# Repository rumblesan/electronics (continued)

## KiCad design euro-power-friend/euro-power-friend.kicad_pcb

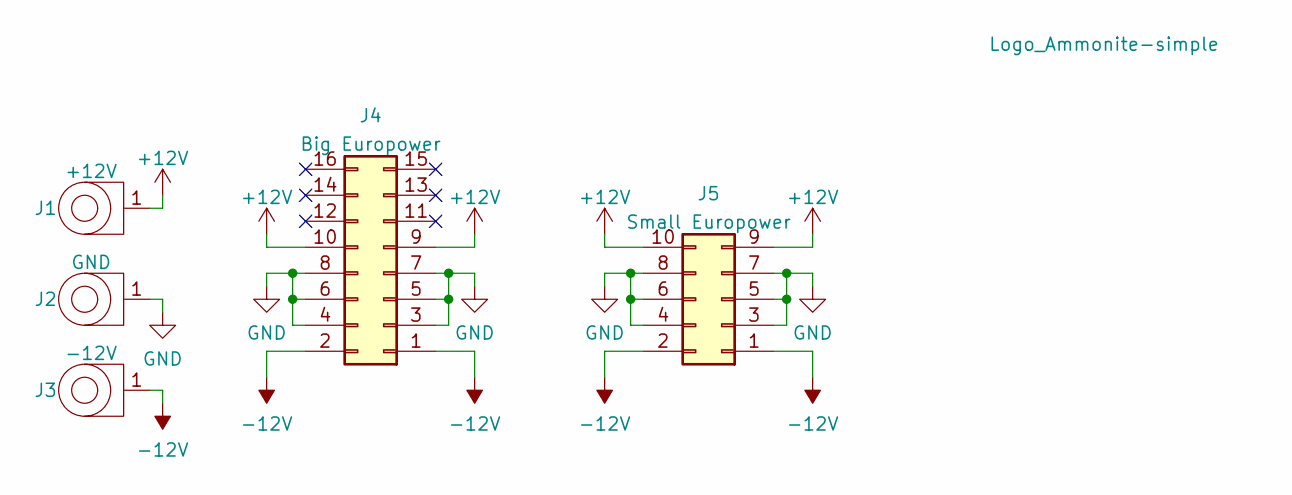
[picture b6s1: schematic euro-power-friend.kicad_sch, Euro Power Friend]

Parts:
H1: Logo_Ammonite-simple; Logo_Ammonite-simple_10.4mmx12.0mm
J1: +12V; Deltron_571_PCB_BananaJack
J2: GND; Deltron_571_PCB_BananaJack
J3: -12V; Deltron_571_PCB_BananaJack
J4: Big Europower; EurorackPowerHeader_2x08_P2.54mm_Shrouded
J5: Small Europower; EurorackPowerHeader_2x05_P2.54mm_Shrouded

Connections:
+12V: J1.1, J4.9, J4.10, J5.9, J5.10
-12V: J3.1, J4.1, J4.2, J5.1, J5.2
GND: J2.1, J4.3, J4.4, J4.5, J4.6, J4.7, J4.8, J5.3, J5.4, J5.5, J5.6, J5.7, J5.8

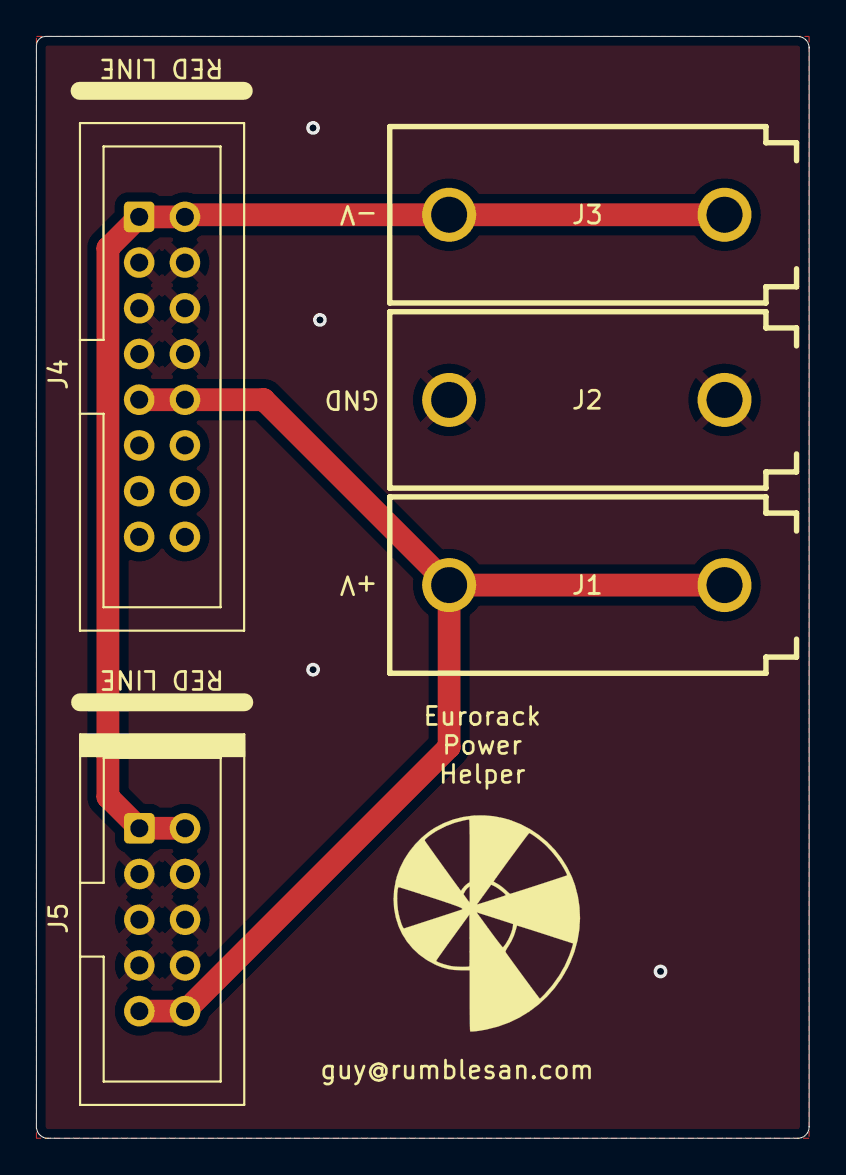
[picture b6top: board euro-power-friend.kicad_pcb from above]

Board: 2 copper layers, 42.9 x 61.2 mm, 6 parts (0 on the bottom side), 3 nets.

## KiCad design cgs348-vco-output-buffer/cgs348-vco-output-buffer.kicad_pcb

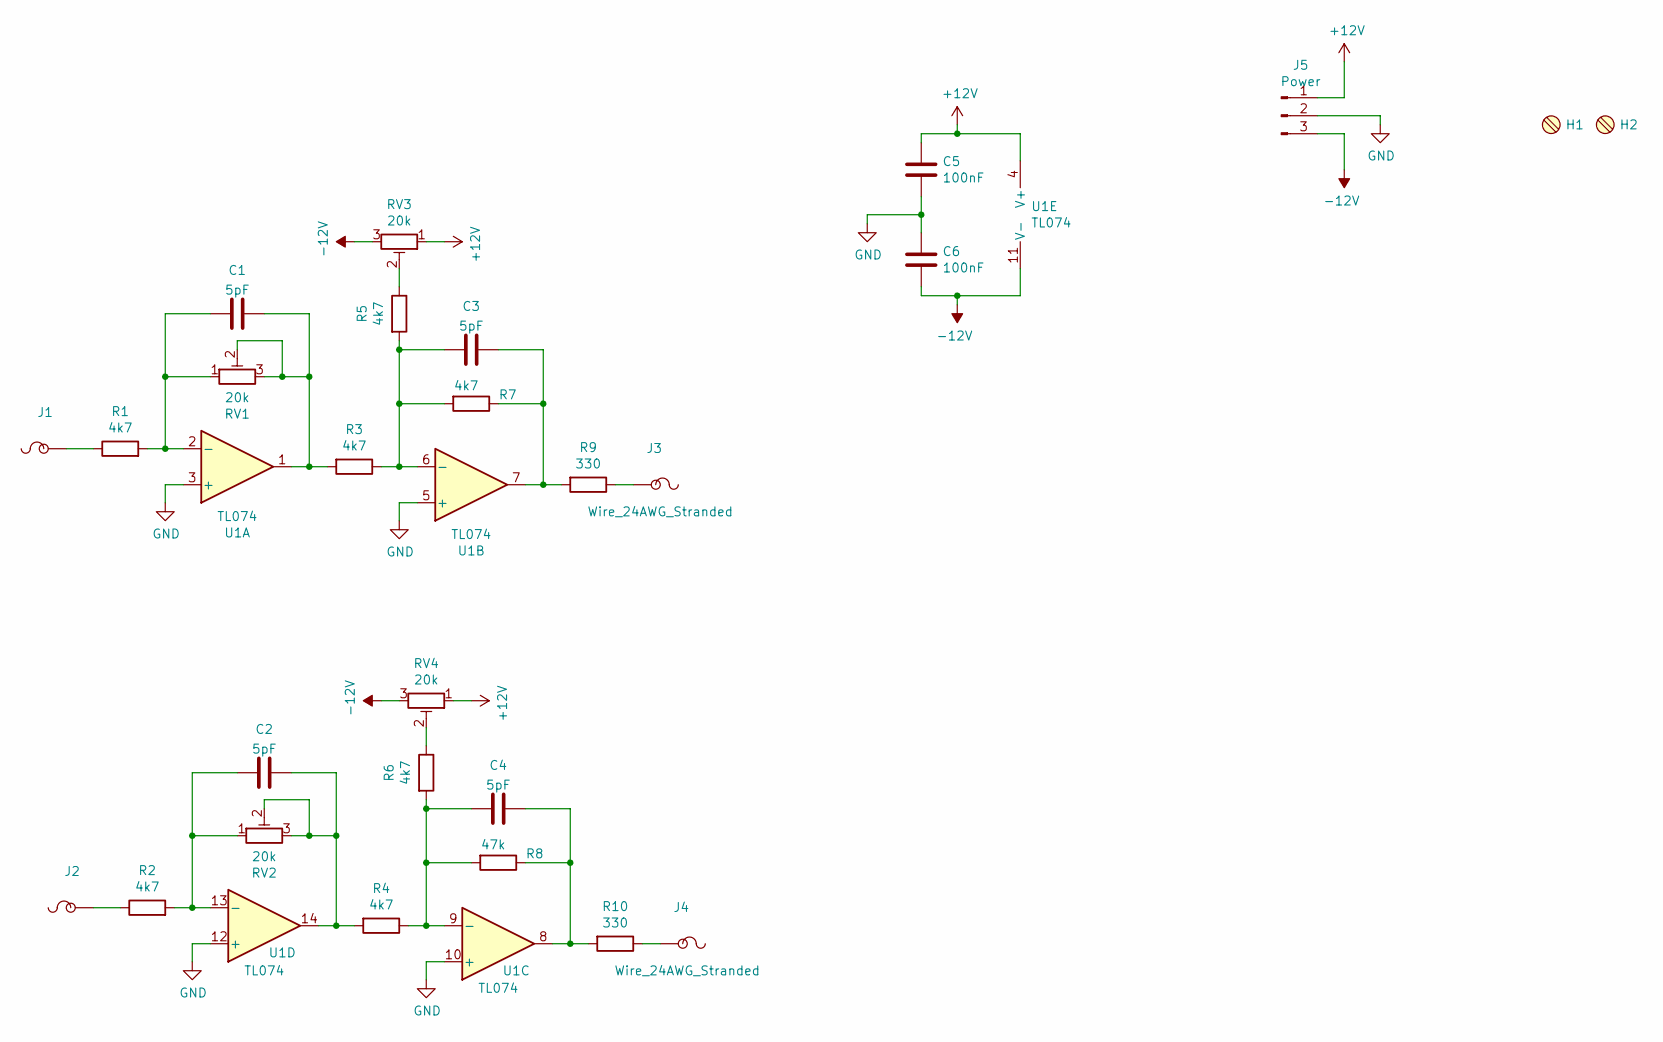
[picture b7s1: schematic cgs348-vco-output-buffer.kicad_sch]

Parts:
C1, C2, C3, C4: 5pF; C_Disc_D4.7mm_W2.5mm_P5.00mm
C5, C6: 100nF; C_Disc_D4.7mm_W2.5mm_P5.00mm
H1, H2: MountingScrew_M3_Flathead; MountingHole_3.2mm_M3
J1, J2, J3, J4: Wire_24AWG_Stranded; SolderWire-24AWG-0.2sqmm_1x01_D0.5mm_OD1.1mm_Relief
J5: Power; SolderWire-24AWG-0.2sqmm_1x03_D0.5mm_OD1.1mm_Relief
R1, R2, R3, R4, R5, R6, R7: 4k7; Resistor_THT_L6.3mm_D2.5mm_P10.16mm_Horizontal
R8: 47k; Resistor_THT_L6.3mm_D2.5mm_P10.16mm_Horizontal
R9, R10: 330; Resistor_THT_L6.3mm_D2.5mm_P10.16mm_Horizontal
RV1, RV2, RV3, RV4: 20k; Potentiometer_THT_Bourns_3306P_Vertical
U1: TL074; DIP-14_W7.62mm_Socket

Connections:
+12V: C5.1, J5.1, RV3.1, RV4.1, U1.4 (V+)
-12V: C6.2, J5.3, RV3.3, RV4.3, U1.11 (V-)
GND: C5.2, C6.1, J5.2, U1.3 (+), U1.5 (+), U1.10 (+), U1.12 (+)
unnamed: C1.1, R1.2, RV1.1, U1.2 (-)
unnamed: C1.2, R3.2, RV1.2, RV1.3, U1.1
unnamed: C2.1, R2.2, RV2.1, U1.13 (-)
unnamed: C2.2, R4.2, RV2.2, RV2.3, U1.14
unnamed: C3.1, R3.1, R5.2, R7.2, U1.6 (-)
unnamed: C3.2, R7.1, R9.2, U1.7
unnamed: C4.1, R4.1, R6.2, R8.2, U1.9 (-)
unnamed: C4.2, R8.1, R10.2, U1.8
unnamed: J1.1, R1.1
unnamed: J2.1, R2.1
unnamed: J3.1, R9.1
unnamed: J4.1, R10.1
unnamed: R5.1, RV3.2
unnamed: R6.1, RV4.2

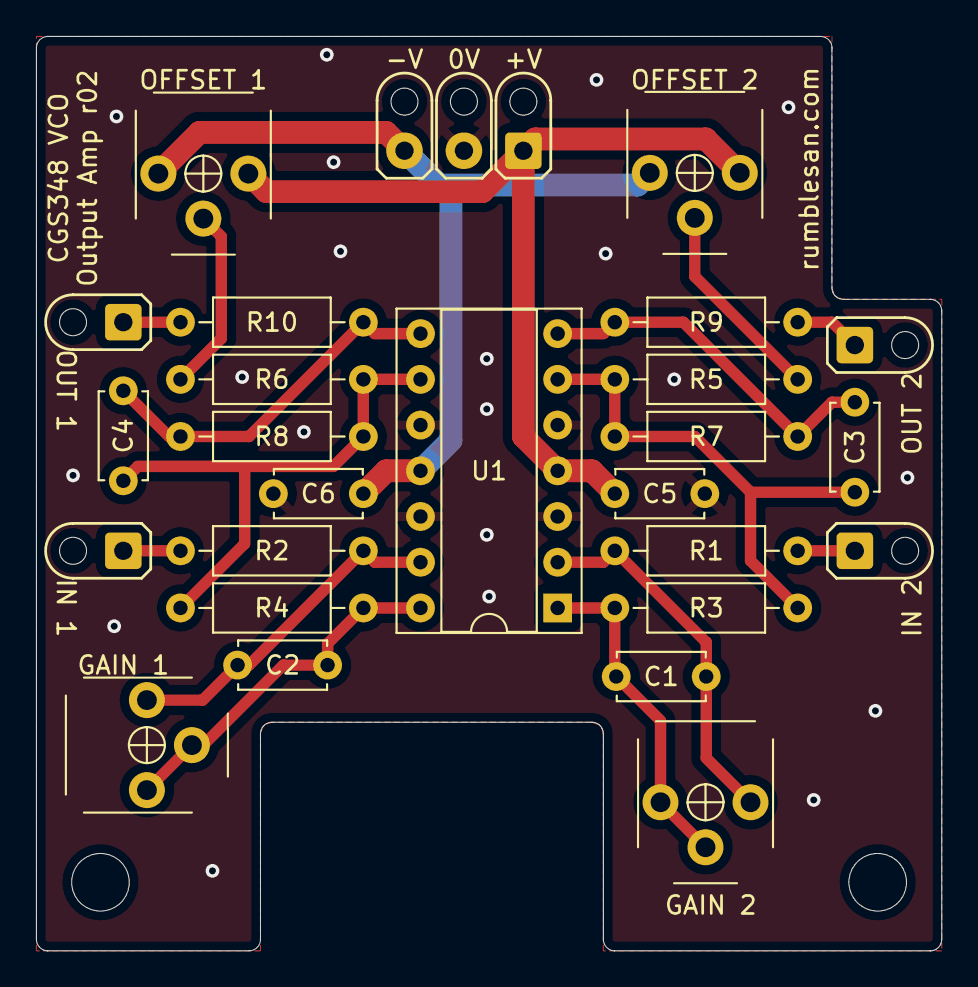
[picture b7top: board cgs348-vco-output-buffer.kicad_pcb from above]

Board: 2 copper layers, 50.3 x 50.8 mm, 28 parts (0 on the bottom side), 17 nets.

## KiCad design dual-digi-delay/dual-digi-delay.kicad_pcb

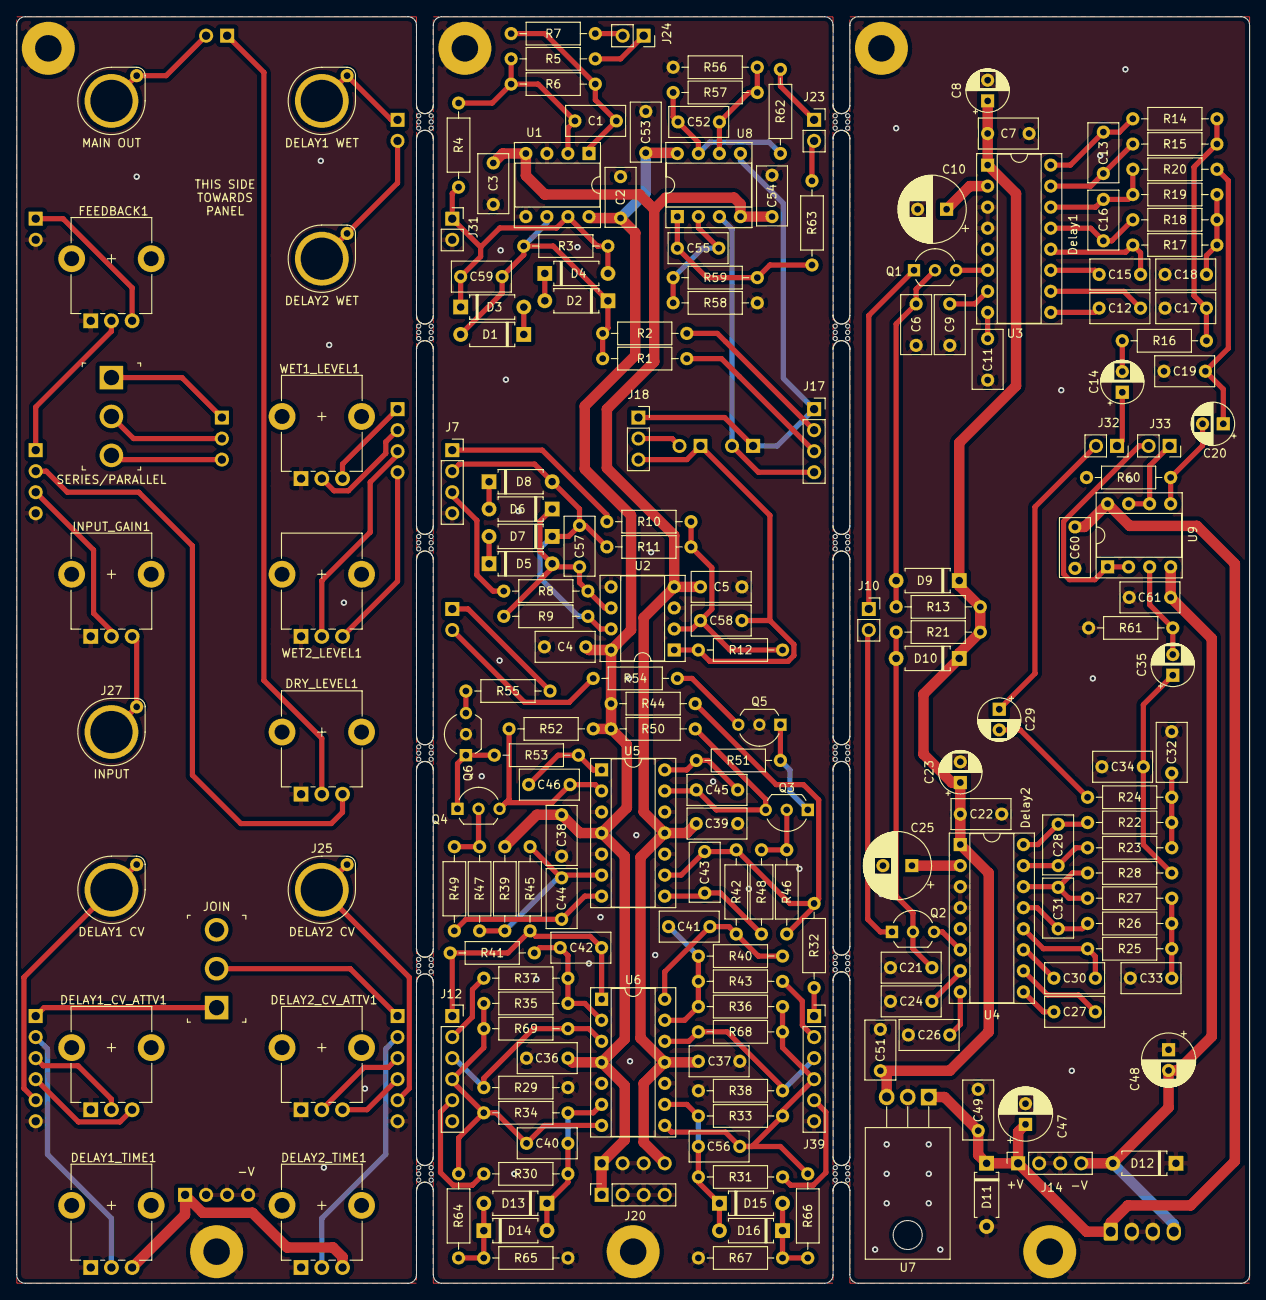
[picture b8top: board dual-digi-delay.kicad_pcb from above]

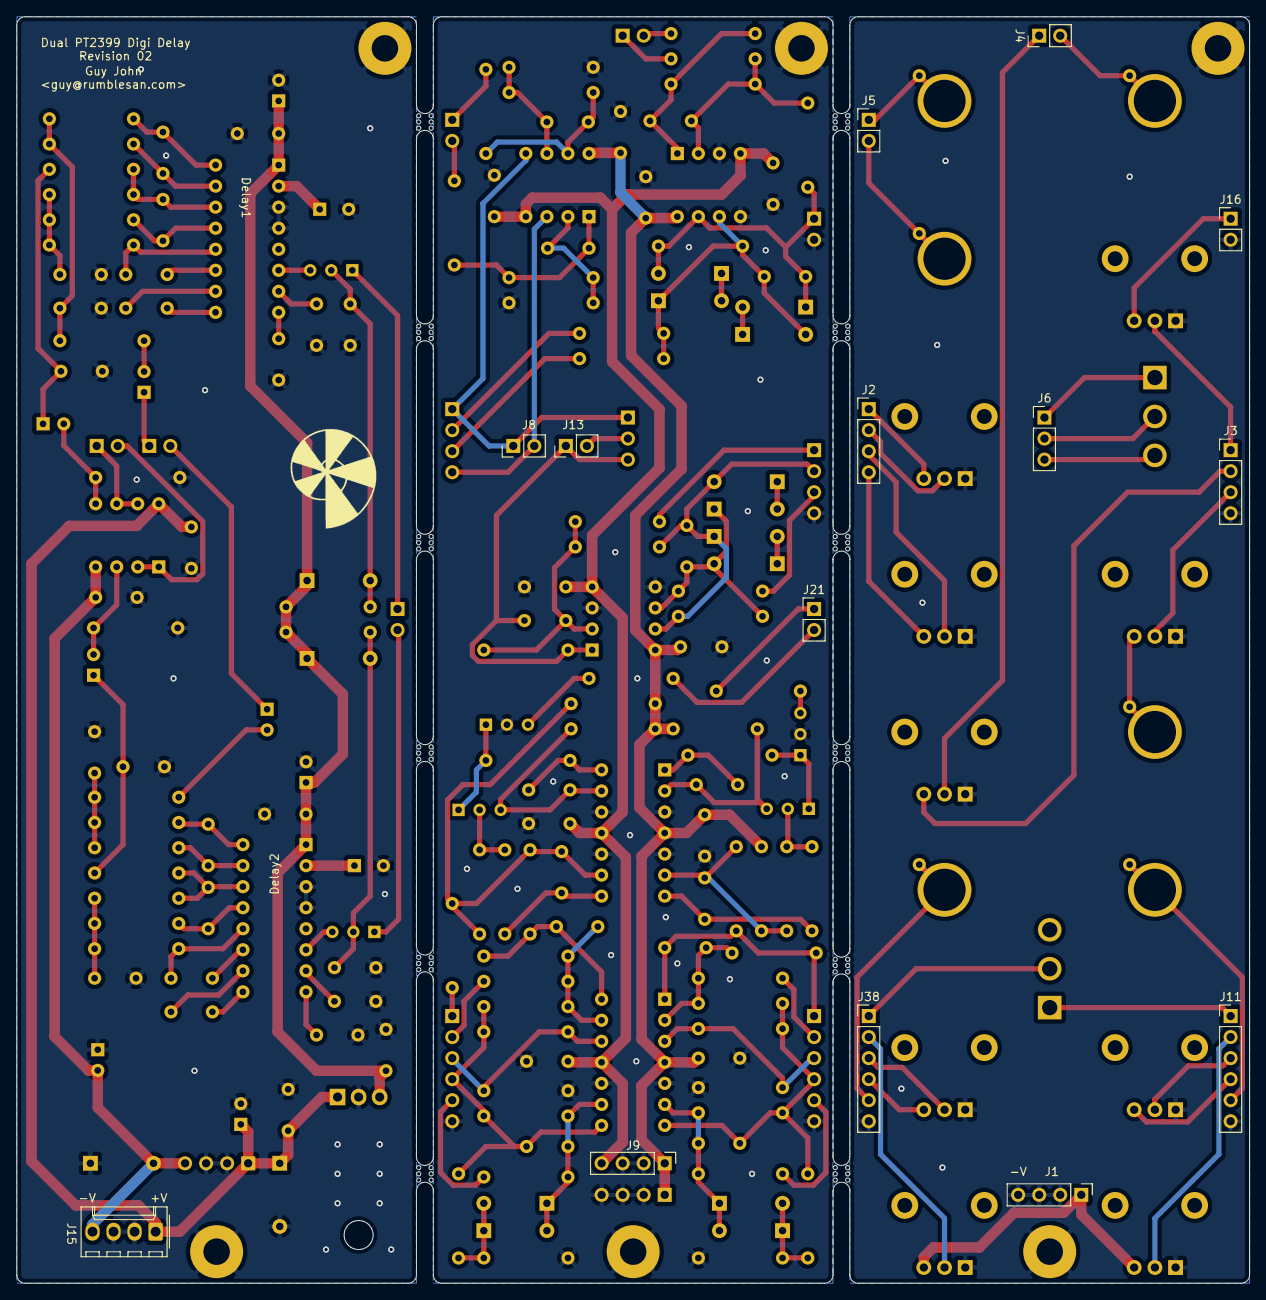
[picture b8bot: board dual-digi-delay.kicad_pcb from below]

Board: 2 copper layers, 148.8 x 152.9 mm, 223 parts (15 on the bottom side), 132 nets.

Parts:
C1, C40, C41, C42, C43, C44, C52, C55, C56, C57, C58, C59: 10pF; C_Rect_L7.0mm_W3.5mm_P5.00mm
C2, C3, C4, C5, C7, C9, C11, C12, C15, C22, C24, C26, C27, C30, C36, C37, C38, C39, C49, C51, C53, C54, C60, C61: 100nF; C_Rect_L7.0mm_W3.5mm_P5.00mm
C6, C21: 470nF; C_Rect_L7.0mm_W3.5mm_P5.00mm
C8, C14, C20, C23, C29, C35: 10uF; CP_Radial_D5.0mm_P2.50mm
C10, C25: 47uF; CP_Radial_D8.0mm_P3.50mm
C13, C16, C28, C31: 560pF; C_Rect_L7.0mm_W3.5mm_P5.00mm
C17, C18, C32, C33: 4n7F (polypropylene); C_Rect_L7.0mm_W3.5mm_P5.00mm
C19, C34: 10nF (polypropylene); C_Rect_L7.0mm_W3.5mm_P5.00mm
C45, C46: 100pF; C_Rect_L7.0mm_W3.5mm_P5.00mm
C47, C48: 10uF; CP_Radial_D6.3mm_P2.50mm
D1, D2, D3, D4, D5, D6, D7, D8: 1N4148; Diode_THT_P7.62mm_Horizontal
D9, D10: 1n4001; Diode_THT_P7.62mm_Horizontal
D11, D12: 1N4001; Diode_THT_P7.62mm_Horizontal
D13, D14, D15, D16: 1n4148; Diode_THT_P7.62mm_Horizontal
DELAY1_CV_ATTV1, DELAY2_CV_ATTV1: 100kB; Potentiometer_Alpha_RD901F-40-00D_Single_Vertical_CircularH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
DELAY1_TIME1, DELAY2_TIME1: 25kB; Potentiometer_Alpha_RD901F-40-00D_Single_Vertical_CircularH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
DRY_LEVEL1: 50kB; Potentiometer_Alpha_RD901F-40-00D_Single_Vertical_CircularH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
FEEDBACK1: 50kB; Potentiometer_Alpha_RD901F-40-00D_Single_Vertical_CircularH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
H1, H2, H3, H4, H5, H6: MountingHole_Pad; MountingHole_3.2mm_M3_Pad
H7, H8, H9, H10, H11, H12, H13, H14, H15, H16, H17, H18: MouseBite; mouse-bite-2mm-slot
H19: Logo_Ammonite-simple; Logo_Ammonite-simple_10.4mmx12.0mm
INPUT_GAIN1: 50kB; Potentiometer_Alpha_RD901F-40-00D_Single_Vertical_CircularH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
J1: TopBoardPowerRecv; PinHeader_1x04_P2.54mm_Vertical
J2: Delay Audio; PinHeader_1x04_P2.54mm_Vertical
J3: Input Audio; PinHeader_1x04_P2.54mm_Vertical
J4: Output Audio; PinHeader_1x02_P2.54mm_Vertical
J5: Delay Out; PinHeader_1x02_P2.54mm_Vertical
J6: Delay2 Source; PinHeader_1x03_P2.54mm_Vertical
J7: Input Audio; PinSocket_1x04_P2.54mm_Vertical
J8: Delay Return; PinHeader_1x02_P2.54mm_Vertical
J9: MidBoardPowerRecv; PinHeader_1x04_P2.54mm_Vertical
J10: Delay Time Control; PinSocket_1x02_P2.54mm_Vertical
J11: Delay1_CV; PinHeader_1x06_P2.54mm_Vertical
J12: Delay1_CV; PinSocket_1x06_P2.54mm_Vertical
J13: Delay Send; PinHeader_1x02_P2.54mm_Vertical
J14: LowerBoardPowerSend; PinSocket_1x04_P2.54mm_Vertical
J15: Main Power; Molex_KK-254_AE-6410-04A_1x04_P2.54mm_Vertical
J16: Feedback Audio; PinHeader_1x02_P2.54mm_Vertical
J17: Delay Audio; PinSocket_1x04_P2.54mm_Vertical
J18: Delay2 Source; PinSocket_1x03_P2.54mm_Vertical
J20: MidBoardPowerSend; PinSocket_1x04_P2.54mm_Vertical
J21: Delay Time Control; PinHeader_1x02_P2.54mm_Vertical
J23: Delay Out; PinSocket_1x02_P2.54mm_Vertical
J24: Output Audio; PinSocket_1x02_P2.54mm_Vertical
J25, J26, J27, J28, J29, J30: BananaJack_PanelMount; BananaJack_THT_JohnsonCinch_108-09
J31: Feedback Audio; PinSocket_1x02_P2.54mm_Vertical
J32: Delay Send; PinSocket_1x02_P2.54mm_Vertical
J33: Delay Return; PinSocket_1x02_P2.54mm_Vertical
J38: Delay2_CV; PinHeader_1x06_P2.54mm_Vertical
J39: Delay2_CV; PinSocket_1x06_P2.54mm_Vertical
Q1, Q2, Q3, Q4, Q5, Q6: 2N3904; TO-92_Inline_Wide
R1, R2, R29, R38, R68, R69: 47k; Resistor_THT_L6.3mm_D2.5mm_P10.16mm_Horizontal
R3, R6, R8, R10, R11, R12, R30, R31, R33, R34, R35, R36, R40, R41, R57, R59, R60, R61: 100k; Resistor_THT_L6.3mm_D2.5mm_P10.16mm_Horizontal
R4, R5, R56, R58: 15k; Resistor_THT_L6.3mm_D2.5mm_P10.16mm_Horizontal
R7, R62, R63: 330r; Resistor_THT_L6.3mm_D2.5mm_P10.16mm_Horizontal
R9: 33k; Resistor_THT_L6.3mm_D2.5mm_P10.16mm_Horizontal
R13, R21, R50, R52: 560k; Resistor_THT_L6.3mm_D2.5mm_P10.16mm_Horizontal
R14, R15, R16, R17, R18, R19, R22, R23, R24, R25, R26, R27, R64, R66: 10k; Resistor_THT_L6.3mm_D2.5mm_P10.16mm_Horizontal
R20, R28: 2k7; Resistor_THT_L6.3mm_D2.5mm_P10.16mm_Horizontal
R32, R42, R45: 56k; Resistor_THT_L6.3mm_D2.5mm_P10.16mm_Horizontal
R37, R43: 220k; Resistor_THT_L6.3mm_D2.5mm_P10.16mm_Horizontal
R39, R44: 150k; Resistor_THT_L6.3mm_D2.5mm_P10.16mm_Horizontal
R46, R47: 2k; Resistor_THT_L6.3mm_D2.5mm_P10.16mm_Horizontal
R48, R49: 22k; Resistor_THT_L6.3mm_D2.5mm_P10.16mm_Horizontal
R51, R53, R65, R67: 1k; Resistor_THT_L6.3mm_D2.5mm_P10.16mm_Horizontal
R54, R55: 470r; Resistor_THT_L6.3mm_D2.5mm_P10.16mm_Horizontal
SW1: SW_SPST; Toggle_Switch_100SP1T1B3M2QE
SW2: SW_SPDT; Toggle_Switch_100SP1T1B3M2QE
U1, U2, U8, U9: TL072; DIP-8_W7.62mm_Socket
U3, U4: PT2399; DIP-16_W7.62mm_Socket
U5, U6: TL074; DIP-14_W7.62mm_Socket
U7: LM7805_TO220; TO-220-3_Horizontal_TabDown
WET1_LEVEL1, WET2_LEVEL1: 50kB; Potentiometer_Alpha_RD901F-40-00D_Single_Vertical_CircularH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

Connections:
+5V: C7.2, C8.1, C22.2, C23.1, C51.2, D9.1, D10.1, R13.1, R21.1, U3.1, U4.1, U7.3
+12V: C2.2, C4.2, C36.2, C38.2, C47.1, C49.2, C53.2, C60.2, D11.1, DELAY1_TIME1.3, DELAY2_TIME1.3, J1.1, J9.1, J14.1, J15.1, J20.1, R39.2, R44.2, R50.1, R52.1, U1.8, U2.8, U5.4, U6.4, U7.1, U8.8, U9.8
-12V: C3.1, C5.1, C37.1, C39.1, C48.2, C54.1, C61.1, D12.2, J9.4, J14.4, J15.4, U1.4, U2.4, U5.11, U6.11, U8.4, U9.4
/AudioIO/AUDIO_IN: INPUT_GAIN1.2, J3.3
/AudioIO/DELAY1_WET: J2.1, WET1_LEVEL1.3
/AudioIO/DELAY1_WET_LEVEL: J2.2, WET1_LEVEL1.2
/AudioIO/DELAY1_WET_OUT: J5.1, J29.1
/AudioIO/DELAY1_WET_TO_2: J6.1, SW2.1
/AudioIO/DELAY2_SOURCE: J6.2, SW2.2
/AudioIO/DELAY2_WET: J2.4, WET2_LEVEL1.3
/AudioIO/DELAY2_WET_LEVEL: J2.3, WET2_LEVEL1.2
/AudioIO/DELAY2_WET_OUT: J5.2, J30.1
/AudioIO/DRY_AUDIO_INPUT: DRY_LEVEL1.3, J3.2
/AudioIO/DRY_AUDIO_LEVEL: DRY_LEVEL1.2, J4.1
/AudioIO/FEEDBACK_INPUT: FEEDBACK1.3, J16.1
/AudioIO/FEEDBACK_LEVEL: FEEDBACK1.2, J3.1
/AudioIO/INPUT_MIX: J6.3, SW2.3
/AudioIO/MAIN_OUT: J4.2, J28.1
/CVControl/DELAY1_CONTROL: J12.2, R37.1
/CVControl/DELAY1_CV_ATTV: J12.3, R29.2, R69.1, U6.3
/CVControl/DELAY1_CV_CTRL: C40.1, J12.4, R34.1, R35.2, R64.1, R69.2, U6.7
/CVControl/DELAY1_CV_INPUT: J12.5, R30.2
/CVControl/DELAY1_CV_JOIN_OUT: C42.1, J12.1, R41.1, R45.2, U6.1
/CVControl/DELAY1_TIME_VOLTAGE: J21.1, R55.1
/CVControl/DELAY2_CONTROL: J39.2, R43.1
/CVControl/DELAY2_CV_ATTV: J39.3, R38.2, R68.1, U6.12
/CVControl/DELAY2_CV_CTRL: C56.1, J39.4, R33.2, R36.2, R66.1, R68.2, U6.8
/CVControl/DELAY2_CV_INPUT: J39.5, R31.1
/CVControl/DELAY2_JOIN_CV_INPUT: J39.1, R32.1
/CVControl/DELAY2_TIME_VOLTAGE: J21.2, R54.1
/CVInputs/DELAY1_CONTROL: DELAY1_TIME1.2, J11.2
/CVInputs/DELAY1_CV_ATTV: DELAY1_CV_ATTV1.2, J11.3
/CVInputs/DELAY1_CV_CTRL: DELAY1_CV_ATTV1.3, J11.4
/CVInputs/DELAY1_CV_INPUT: J11.5, J26.1
/CVInputs/DELAY2_CONTROL: DELAY2_TIME1.2, J38.2
/CVInputs/DELAY2_CV_ATTV: DELAY2_CV_ATTV1.2, J38.3
/CVInputs/DELAY2_CV_CTRL: DELAY2_CV_ATTV1.3, J38.4
/CVInputs/DELAY2_CV_INPUT: J25.1, J38.5
/CVInputs/JOIN_CV: J38.1, SW1.2
/CVInputs/JOIN_CV_SOURCE: J11.1, SW1.1
/DelayBuffers/DELAY1_OUT: J33.1, U9.6, U9.7
/DelayBuffers/DELAY2_OUT: J33.2, U9.1, U9.2
/DelayOut/DELAY1_WET: J8.1, J17.1, J18.1, U8.5
/DelayOut/DELAY1_WET_OUT: J23.1, R62.1
/DelayOut/DELAY2_WET: J8.2, J17.4, U8.3
/DelayOut/DELAY2_WET_OUT: J23.2, R63.1
/InputMix/AUDIO_IN: J7.3, R8.2
/InputMix/DELAY_FEEDBACK: J7.1, R10.2
/InputMix/DRY_AUDIO_SOURCE: C57.1, D7.1, D8.2, J7.2, R9.1, R11.2, U2.7
/InputMix/INPUT_MIX: C58.1, J13.1, J18.3, R12.1, U2.1
/OutputMix/DELAY1_WET_LEVEL: J17.2, R2.2
/OutputMix/DELAY2_WET_LEVEL: J17.3, R1.2
/OutputMix/DELAY_MIX: C59.1, D3.1, D4.2, J31.1, R3.1, R4.2, U1.7
/OutputMix/DRY_AUDIO_INPUT: J24.1, R5.1
/OutputMix/MIX_OUT: J24.2, R7.1
/PT2399-Delay-1/AUDIO_IN: C14.1, J32.1
/PT2399-Delay-1/AUDIO_OUT: C20.2, R60.1, U9.5
/PT2399-Delay-1/DELAY_TIME_CTRL: J10.1, Q1.1
/PT2399-Delay-2/AUDIO_IN: C29.1, J32.2
/PT2399-Delay-2/AUDIO_OUT: C35.2, R61.1, U9.3
/PT2399-Delay-2/DELAY_TIME_CTRL: J10.2, Q2.1
GND: C2.1, C3.2, C4.1, C5.2, C6.2, C7.1, C8.2, C9.1, C10.2, C11.1, C17.1, C18.1, C19.1, C21.2, C22.1, C23.2, C24.1, C25.2, C26.1, C32.1, C33.1, C34.1, C36.1, C37.2, C38.1, C39.2, C47.2, C48.1, C49.1, C51.1, C53.1, C54.2, C60.1, C61.2, D11.2, D12.1, DELAY1_CV_ATTV1.1, DELAY1_TIME1.1, DELAY2_CV_ATTV1.1, DELAY2_TIME1.1, DRY_LEVEL1.1, FEEDBACK1.1, H1.1, H2.1, H3.1, H4.1, H5.1, H6.1, INPUT_GAIN1.1, J1.2, J1.3, J1.4, J3.4, J7.4, J9.2, J9.3, J11.6, J12.6, J14.2, J14.3, J15.2, J15.3, J16.2, J20.2, J20.3, J20.4, J31.2, J38.6, J39.6, Q5.2, Q6.2, R29.1, R38.1, R56.1, R58.1, R60.2, R61.2, R65.1, R67.1, U1.3, U1.5, U2.3, U2.5, U3.3, U3.4, U4.3, U4.4, U5.3, U5.5, U5.10, U5.12, U6.5, U6.10, U7.2, WET1_LEVEL1.1, WET2_LEVEL1.1
unnamed: C1.1, R6.1, R7.2, U1.1
unnamed: C1.2, R4.1, R5.2, R6.2, U1.2
unnamed: C6.1, D9.2, Q1.2, R13.2
unnamed: C9.2, U3.7
unnamed: C10.1, U3.2
unnamed: C11.2, U3.8
unnamed: C12.1, U3.9
unnamed: C12.2, U3.10
unnamed: C13.1, R15.2, U3.15
unnamed: C13.2, R14.2, U3.16
unnamed: C14.2, R16.2
unnamed: C15.1, U3.11
unnamed: C15.2, R17.2, U3.12
unnamed: C16.1, R19.2, R20.2, U3.14
unnamed: C16.2, R18.2, U3.13
unnamed: C17.2, R14.1, R15.1, R16.1
unnamed: C18.2, R17.1, R18.1, R19.1
unnamed: C19.2, C20.1, R20.1
unnamed: C21.1, D10.2, Q2.2, R21.2
unnamed: C24.2, U4.7
unnamed: C25.1, U4.2
unnamed: C26.2, U4.8
unnamed: C27.1, U4.9
unnamed: C27.2, U4.10
unnamed: C28.1, R23.2, U4.15
unnamed: C28.2, R22.2, U4.16
unnamed: C29.2, R24.2
unnamed: C30.1, U4.11
unnamed: C30.2, R25.2, U4.12
unnamed: C31.1, R27.2, R28.2, U4.14
unnamed: C31.2, R26.2, U4.13
unnamed: C32.2, R22.1, R23.1, R24.1
unnamed: C33.2, R25.1, R26.1, R27.1
unnamed: C34.2, C35.1, R28.1
unnamed: C40.2, D13.1, D14.2, R30.1, R34.2, U6.6
unnamed: C41.1, R40.1, R42.2, U6.14
unnamed: C41.2, R36.1, R40.2, R43.2, U6.13
unnamed: C42.2, R35.1, R37.2, R41.2, U6.2
unnamed: C43.1, R48.1, U5.8
unnamed: C43.2, R32.2, R42.1, R44.1, R46.2, U5.9
unnamed: C44.1, R49.1, U5.7
unnamed: C44.2, R39.1, R45.1, R47.2, U5.6
unnamed: C45.1, Q3.3, R50.2, U5.13
unnamed: C45.2, R51.2, U5.14
unnamed: C46.1, Q4.3, R52.2, U5.2
unnamed: C46.2, R53.2, U5.1
unnamed: C52.1, R57.1, R62.2, U8.7
unnamed: C52.2, R56.2, R57.2, U8.6
unnamed: C55.1, R59.1, R63.2, U8.1
unnamed: C55.2, R58.2, R59.2, U8.2
unnamed: C56.2, D15.1, D16.2, R31.2, R33.1, U6.9
unnamed: C57.2, D5.2, D6.1, R8.1, R9.2, U2.6
unnamed: C58.2, R10.1, R11.1, R12.2, U2.2
unnamed: C59.2, D1.2, D2.1, R1.1, R2.1, R3.2, U1.6
unnamed: D1.1, D3.2
unnamed: D2.2, D4.1
unnamed: D5.1, D7.2
unnamed: D6.2, D8.1
unnamed: D13.2, D14.1, R64.2, R65.2
unnamed: D15.2, D16.1, R66.2, R67.2
unnamed: INPUT_GAIN1.3, J27.1
unnamed: J13.2, J18.2
unnamed: Q1.3, U3.6
unnamed: Q2.3, U4.6
unnamed: Q3.1, Q5.1, R51.1
unnamed: Q3.2, R46.1, R48.2
unnamed: Q4.1, Q6.1, R53.1
unnamed: Q4.2, R47.1, R49.2
unnamed: Q5.3, R54.2
unnamed: Q6.3, R55.2

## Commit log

2021-02-18 Adding readme and license files
2021-02-19 Adding screws to mixer schematic
2021-03-26 Adding beginnings of 3350 VCF
2021-06-19 More stuff on 3350 vcf
2021-06-19 Adding breadboard power distrib
2021-06-19 Adding transistor matcher
2021-06-20 More updates to gain cell
2021-06-26 breadboard power distrib tweaks
2021-06-26 Adding cgs attenuverter board project
2021-06-26 Adding cgs348 vco output buffer project
2021-06-30 Updating ordered boards
2021-07-05 Adding 4u mini boat power connection project
2021-07-08 Adding gerbers for mini boat power distrib
2021-07-08 Adding multiple projects
    music thing spring reverb
    music thing vactrol crossfader
    serge r6 vca/ringmod
2021-07-09 adding opamp feedback caps to dc mixer
2021-07-14 Updates to attenuverter board
2021-07-14 Tweak transistor matcher and generate gerbers
2021-08-02 Updated version of music thing spring reverb
2021-08-02 Adding banana bread board helpers
2021-08-04 Adding serge vcfs schematic
2021-08-10 Tweaks to transistor matcher
2021-08-10 Updating spring reverb to rev3
2021-08-10 Updating spring reverb to remove music thing name
    Still noted that it's based on the MT reverb though
2021-08-25 Renaming serge vcfq project
2021-09-07 Updating spring reverb
2021-09-07 Adding 4u 2col blank ammonite design panel
2021-10-04 Fixing issue with vcfs
2021-10-04 Deleting psu audio output circuit
2021-10-04 Fixing issue with serge vcfq
2021-10-04 Updating serge r6 gate
2021-10-26 Final revision of dual digi delay
2021-10-26 Adding digi delay gerbers
2021-10-30 Adding spirals and tiles blank
2021-10-30 Finalising rev 01 of dual digi delay
2021-11-01 Adding 4u boat power distribution project
2021-11-09 Adding serge vcf2
2021-12-18 Updating digi delay to rev 2
2021-12-31 Updating 348 vco output buffer
2022-01-01 Switch dual digi delay to use kicad6
2022-01-01 Switch 348 output buffer to kicad6
2022-01-14 Creating revision 3 of dual digi delay
2022-01-16 Making temporary branch for rev2 builds
2022-01-17 Dual digi delay moved to its own repo
2022-04-22 Adding euro power friend
2022-05-06 Adding simple integrator chaos suite circuit
2022-05-07 Adding first chaos suite modules
2022-05-21 Laying out damped integrator pcb
2022-05-21 Removing old files
2022-05-21 adding more panel stuff for damped integrators
2022-06-17 Adding icl7660 negative supply adapter
2022-06-17 Adding panel files
2022-06-17 Final tweaks to simple integrator
2022-06-17 final damped integrator tweaks
2022-06-17 Tweaking blank panel projects
2022-06-17 update iclc7660 adapter with new footprints
2022-06-29 Creating gerbers for negative supply adapter
2022-06-29 finalising rev01 of simple integrator
2022-07-25 Updating damped integrator circuit and layout
2022-09-03 Updating simple integrator to rev2
2022-09-03 Updating variable integrator
2022-09-03 Adding tws module project
2022-09-04 Updating banana bread board helper
2022-09-04 Moving blank panels into synth panels repo
2022-09-04 Adding beginnings of 4u line in
2022-09-04 Moving chaos suite to its own repo
